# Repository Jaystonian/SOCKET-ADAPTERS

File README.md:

# SOCKET-ADAPTERS
Various adapters for ICs

23xxxAdapter: Eprom 27128/27256/27512 (28pin) to a 2332 or 2364 socket (24pin)

27xxx_to_27c080: Eprom 27c010 to 27c080 (32pin) to a 27256 or 27512 socket (28pin)

6502-65816: CPU WDC65C816 (16bit) to a 6502 (VIC-20, PET)

74LS12: Recreated the 7412 (discontinued) with a 7411 and 7406.  Use LS, HCT, AHCT or LV-A.

DIP48-XC9572XL: Xilinx CPLD to fit 48pin for C128 MMU, PLA etc.

LM323K: Triple TO-220 to fit a TO-3 (VIC-20 regulator replacement)

dipXXsoic: Fit soic-XX to dip-XX
dipXXtssop: fit tssop-XX to dip-XX
dip20soic573-373: Fit an SOIC-20 74573 to a DIP-20 74373 socket.
dip20tssop573-373: Fit a TSSOP-20 74573 to a DIP-20 74373 socket.

pi1541translator: Fit a TXS0104 4-bit level translator to a Raspberry Pi 1541 PCB as the translator unit

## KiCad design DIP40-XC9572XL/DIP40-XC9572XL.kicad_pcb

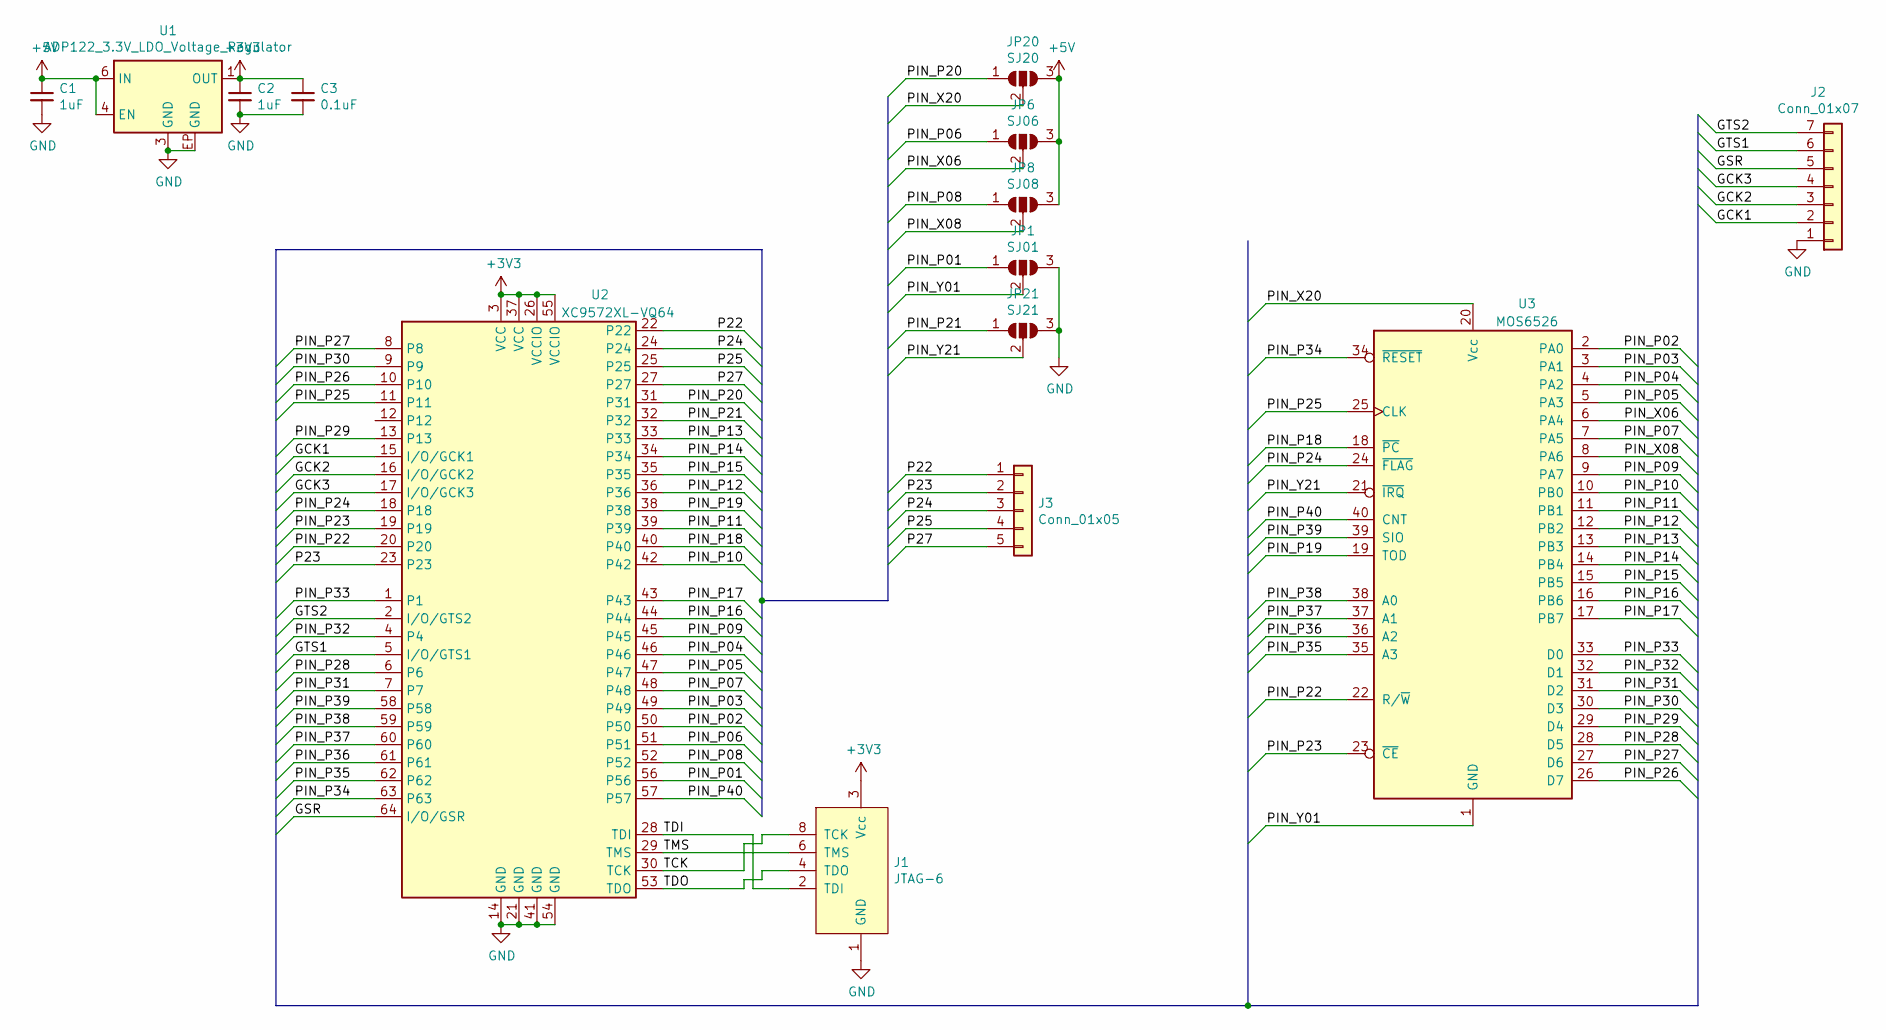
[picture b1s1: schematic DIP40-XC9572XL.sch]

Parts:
C1, C2: 1uF; C_0805_2012Metric_Pad1.15x1.40mm_HandSolder
C3: 0.1uF; C_0805_2012Metric_Pad1.15x1.40mm_HandSolder
J1: JTAG-6; PinHeader_2x04_P2.54mm_Vertical
J2: Conn_01x07; PinHeader_1x07_P2.54mm_Vertical_SMD_Pin1Right
J3: Conn_01x05; PinHeader_1x05_P1.27mm_Vertical
JP1: SJ01; SolderJumper-3_P1.3mm_Open_RoundedPad1.0x1.5mm_NumberLabels
JP6: SJ06; SolderJumper-3_P1.3mm_Open_RoundedPad1.0x1.5mm_NumberLabels
JP8: SJ08; SolderJumper-3_P1.3mm_Open_RoundedPad1.0x1.5mm_NumberLabels
JP20: SJ20; SolderJumper-3_P1.3mm_Open_RoundedPad1.0x1.5mm_NumberLabels
JP21: SJ21; SolderJumper-3_P1.3mm_Open_RoundedPad1.0x1.5mm_NumberLabels
U1: ADP122_3.3V_LDO_Voltage_Regulator; LFCSP-6
U2: XC9572XL-VQ64; TQFP-64_10x10mm_P0.5mm
U3: MOS6526; DIP-40_W15.24mm

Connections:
+3V3: C2.1, C3.1, J1.3 (Vcc), U1.1 (OUT), U2.3 (VCC), U2.26 (VCCIO), U2.37 (VCC), U2.55 (VCCIO)
+5V: C1.1, JP6.3 (B), JP8.3 (B), JP20.3 (B), U1.4 (EN), U1.6 (IN)
/GCK1: J2.2, U2.15 (I/O/GCK1)
/GCK2: J2.3, U2.16 (I/O/GCK2)
/GCK3: J2.4, U2.17 (I/O/GCK3)
/GSR: J2.5, U2.64 (I/O/GSR)
/GTS1: J2.6, U2.5 (I/O/GTS1)
/GTS2: J2.7, U2.2 (I/O/GTS2)
/P22: J3.1, U2.22
/P23: J3.2, U2.23
/P24: J3.3, U2.24
/P25: J3.4, U2.25
/P27: J3.5, U2.27
/PIN_P01: JP1.1 (A), U2.56
/PIN_P02: U2.50, U3.2 (PA0)
/PIN_P03: U2.49, U3.3 (PA1)
/PIN_P04: U2.46, U3.4 (PA2)
/PIN_P05: U2.47, U3.5 (PA3)
/PIN_P06: JP6.1 (A), U2.51
/PIN_P07: U2.48, U3.7 (PA5)
/PIN_P08: JP8.1 (A), U2.52
/PIN_P09: U2.45, U3.9 (PA7)
/PIN_P10: U2.42, U3.10 (PB0)
/PIN_P11: U2.39, U3.11 (PB1)
/PIN_P12: U2.36, U3.12 (PB2)
/PIN_P13: U2.33, U3.13 (PB3)
/PIN_P14: U2.34, U3.14 (PB4)
/PIN_P15: U2.35, U3.15 (PB5)
/PIN_P16: U2.44, U3.16 (PB6)
/PIN_P17: U2.43, U3.17 (PB7)
/PIN_P18: U2.40, U3.18 (~PC~)
/PIN_P19: U2.38, U3.19 (TOD)
/PIN_P20: JP20.1 (A), U2.31
/PIN_P21: JP21.1 (A), U2.32
/PIN_P22: U2.20, U3.22 (R/~W~)
/PIN_P23: U2.19, U3.23 (~CE~)
/PIN_P24: U2.18, U3.24 (~FLAG~)
/PIN_P25: U2.11, U3.25 (CLK)
/PIN_P26: U2.10, U3.26 (D7)
/PIN_P27: U2.8, U3.27 (D6)
/PIN_P28: U2.6, U3.28 (D5)
/PIN_P29: U2.13, U3.29 (D4)
/PIN_P30: U2.9, U3.30 (D3)
/PIN_P31: U2.7, U3.31 (D2)
/PIN_P32: U2.4, U3.32 (D1)
/PIN_P33: U2.1, U3.33 (D0)
/PIN_P34: U2.63, U3.34 (~RESET~)
/PIN_P35: U2.62, U3.35 (A3)
/PIN_P36: U2.61, U3.36 (A2)
/PIN_P37: U2.60, U3.37 (A1)
/PIN_P38: U2.59, U3.38 (A0)
/PIN_P39: U2.58, U3.39 (SIO)
/PIN_P40: U2.57, U3.40 (CNT)
/PIN_X06: JP6.2 (C), U3.6 (PA4)
/PIN_X08: JP8.2 (C), U3.8 (PA6)
/PIN_X20: JP20.2 (C), U3.20 (Vcc)
/PIN_Y01: JP1.2 (C), U3.1 (GND)
/PIN_Y21: JP21.2 (C), U3.21 (~IRQ~)
/TCK: J1.8 (TCK), U2.30 (TCK)
/TDI: J1.2 (TDI), U2.28 (TDI)
/TDO: J1.4 (TDO), U2.53 (TDO)
/TMS: J1.6 (TMS), U2.29 (TMS)
GND: C1.2, C2.2, C3.2, J1.1 (GND), J2.1, JP1.3 (B), JP21.3 (B), U1.3 (GND), U1.EP (GND), U2.14 (GND), U2.21 (GND), U2.41 (GND), U2.54 (GND)

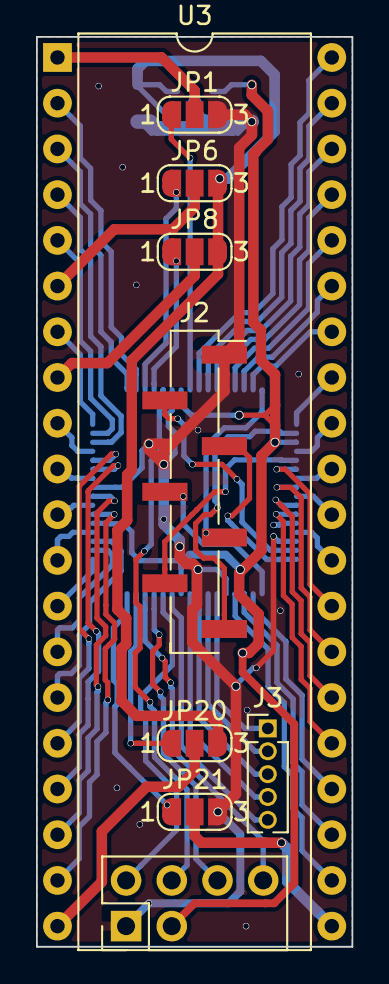
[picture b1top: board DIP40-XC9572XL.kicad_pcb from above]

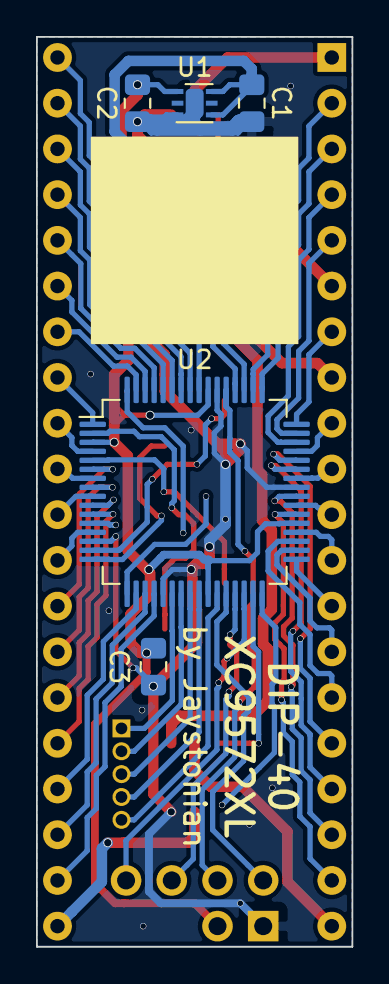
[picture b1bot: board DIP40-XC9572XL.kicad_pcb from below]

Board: 2 copper layers, 17.5 x 50.5 mm, 14 parts (5 on the bottom side), 63 nets.

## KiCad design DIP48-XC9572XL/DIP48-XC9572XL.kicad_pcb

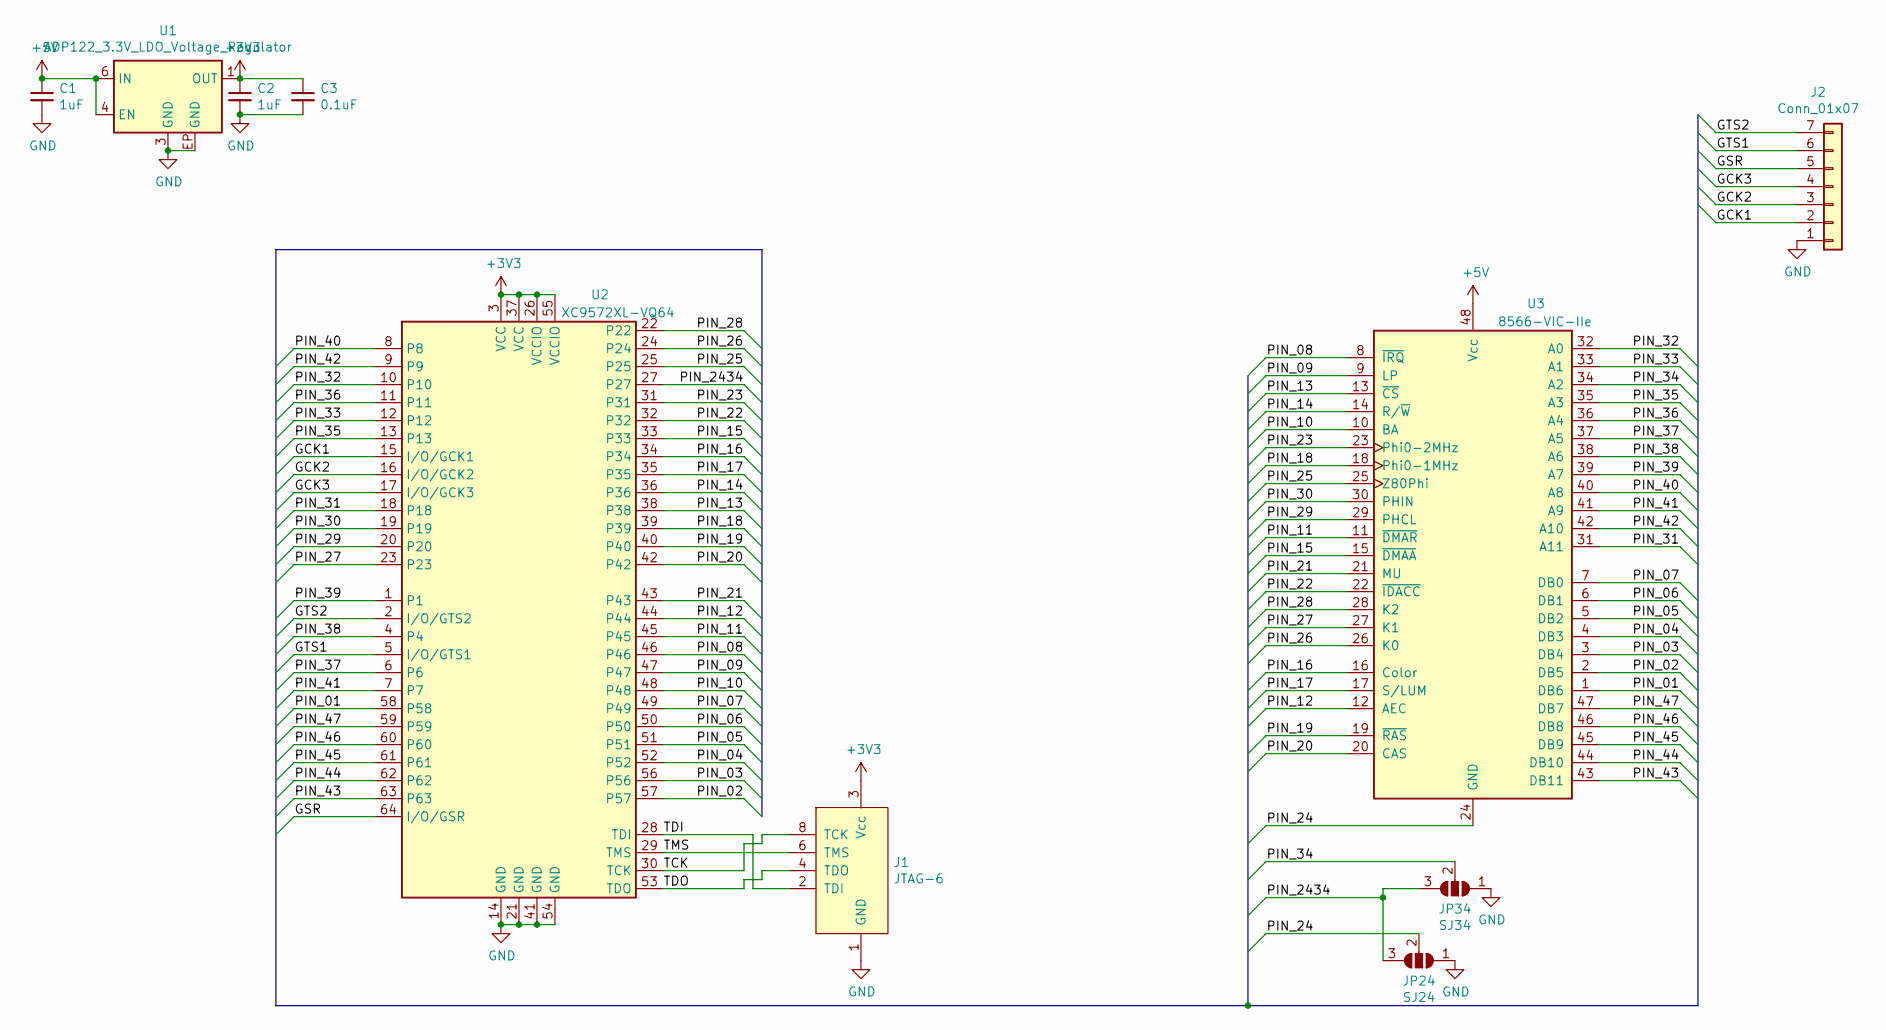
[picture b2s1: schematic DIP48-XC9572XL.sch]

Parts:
C1, C2: 1uF; C_0805_2012Metric_Pad1.15x1.40mm_HandSolder
C3: 0.1uF; C_0805_2012Metric_Pad1.15x1.40mm_HandSolder
J1: JTAG-6; PinHeader_2x04_P2.54mm_Vertical
J2: Conn_01x07; PinHeader_1x07_P2.54mm_Vertical_SMD_Pin1Right
JP24: SJ24; SolderJumper-3_P1.3mm_Open_RoundedPad1.0x1.5mm_NumberLabels
JP34: SJ34; SolderJumper-3_P1.3mm_Open_RoundedPad1.0x1.5mm_NumberLabels
U1: ADP122_3.3V_LDO_Voltage_Regulator; LFCSP-6
U2: XC9572XL-VQ64; TQFP-64_10x10mm_P0.5mm
U3: 8566-VIC-IIe; DIP-48_W15.24mm

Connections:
+3V3: C2.1, C3.1, J1.3 (Vcc), U1.1 (OUT), U2.3 (VCC), U2.26 (VCCIO), U2.37 (VCC), U2.55 (VCCIO)
+5V: C1.1, U1.4 (EN), U1.6 (IN), U3.48 (Vcc)
/GCK1: J2.2, U2.15 (I/O/GCK1)
/GCK2: J2.3, U2.16 (I/O/GCK2)
/GCK3: J2.4, U2.17 (I/O/GCK3)
/GSR: J2.5, U2.64 (I/O/GSR)
/GTS1: J2.6, U2.5 (I/O/GTS1)
/GTS2: J2.7, U2.2 (I/O/GTS2)
/PIN_01: U2.58, U3.1 (DB6)
/PIN_02: U2.57, U3.2 (DB5)
/PIN_03: U2.56, U3.3 (DB4)
/PIN_04: U2.52, U3.4 (DB3)
/PIN_05: U2.51, U3.5 (DB2)
/PIN_06: U2.50, U3.6 (DB1)
/PIN_07: U2.49, U3.7 (DB0)
/PIN_08: U2.46, U3.8 (~IRQ~)
/PIN_09: U2.47, U3.9 (LP)
/PIN_10: U2.48, U3.10 (BA)
/PIN_11: U2.45, U3.11 (~DMAR)
/PIN_12: U2.44, U3.12 (AEC)
/PIN_13: U2.38, U3.13 (~CS~)
/PIN_14: U2.36, U3.14 (R/~W~)
/PIN_15: U2.33, U3.15 (~DMAA)
/PIN_16: U2.34, U3.16 (Color)
/PIN_17: U2.35, U3.17 (S/LUM)
/PIN_18: U2.39, U3.18 (Phi0-1MHz)
/PIN_19: U2.40, U3.19 (~RAS~)
/PIN_20: U2.42, U3.20 (CAS)
/PIN_21: U2.43, U3.21 (MU)
/PIN_22: U2.32, U3.22 (~IDACC)
/PIN_23: U2.31, U3.23 (Phi0-2MHz)
/PIN_24: JP24.2 (C), U3.24 (GND)
/PIN_25: U2.25, U3.25 (Z80Phi)
/PIN_26: U2.24, U3.26 (K0)
/PIN_27: U2.23, U3.27 (K1)
/PIN_28: U2.22, U3.28 (K2)
/PIN_29: U2.20, U3.29 (PHCL)
/PIN_30: U2.19, U3.30 (PHIN)
/PIN_31: U2.18, U3.31 (A11)
/PIN_32: U2.10, U3.32 (A0)
/PIN_33: U2.12, U3.33 (A1)
/PIN_34: JP34.2 (C), U3.34 (A2)
/PIN_35: U2.13, U3.35 (A3)
/PIN_36: U2.11, U3.36 (A4)
/PIN_37: U2.6, U3.37 (A5)
/PIN_38: U2.4, U3.38 (A6)
/PIN_39: U2.1, U3.39 (A7)
/PIN_40: U2.8, U3.40 (A8)
/PIN_41: U2.7, U3.41 (A9)
/PIN_42: U2.9, U3.42 (A10)
/PIN_43: U2.63, U3.43 (DB11)
/PIN_44: U2.62, U3.44 (DB10)
/PIN_45: U2.61, U3.45 (DB9)
/PIN_46: U2.60, U3.46 (DB8)
/PIN_47: U2.59, U3.47 (DB7)
/PIN_2434: JP24.3 (B), JP34.3 (B), U2.27
/TCK: J1.8 (TCK), U2.30 (TCK)
/TDI: J1.2 (TDI), U2.28 (TDI)
/TDO: J1.4 (TDO), U2.53 (TDO)
/TMS: J1.6 (TMS), U2.29 (TMS)
GND: C1.2, C2.2, C3.2, J1.1 (GND), J2.1, JP24.1 (A), JP34.1 (A), U1.3 (GND), U1.EP (GND), U2.14 (GND), U2.21 (GND), U2.41 (GND), U2.54 (GND)

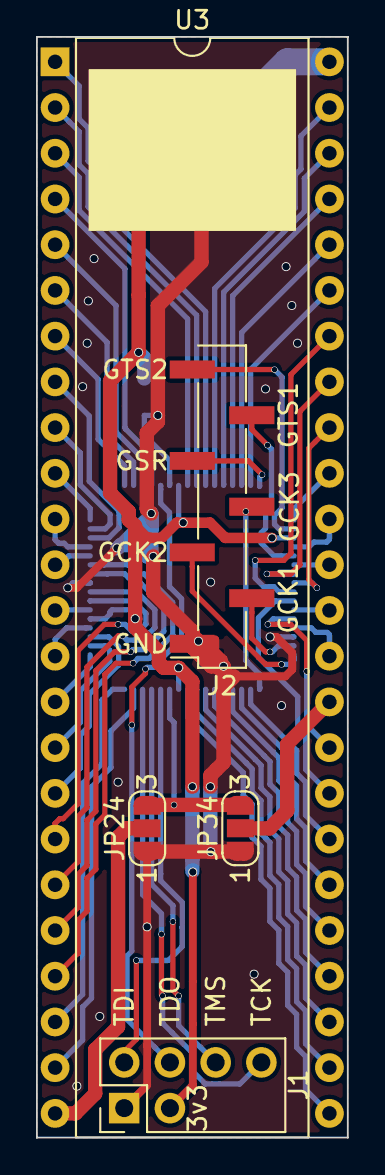
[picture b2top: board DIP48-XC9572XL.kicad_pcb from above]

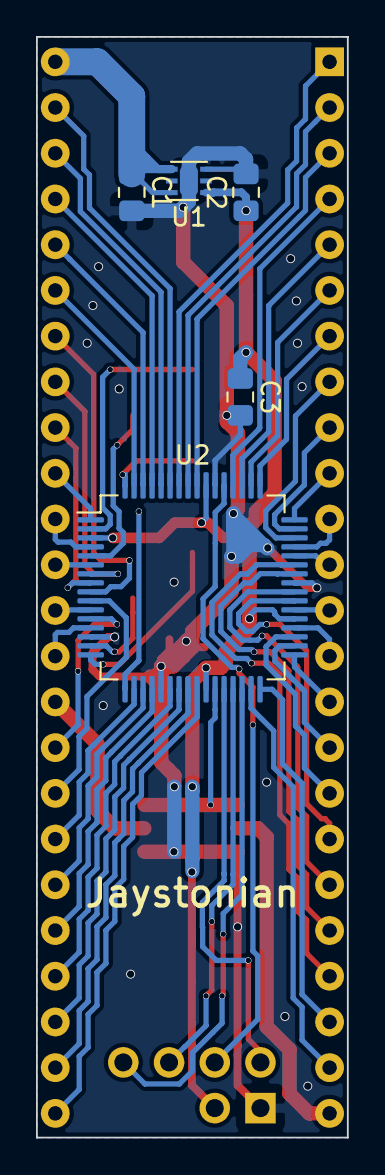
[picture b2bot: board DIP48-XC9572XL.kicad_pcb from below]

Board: 2 copper layers, 17.3 x 61.2 mm, 10 parts (5 on the bottom side), 61 nets.

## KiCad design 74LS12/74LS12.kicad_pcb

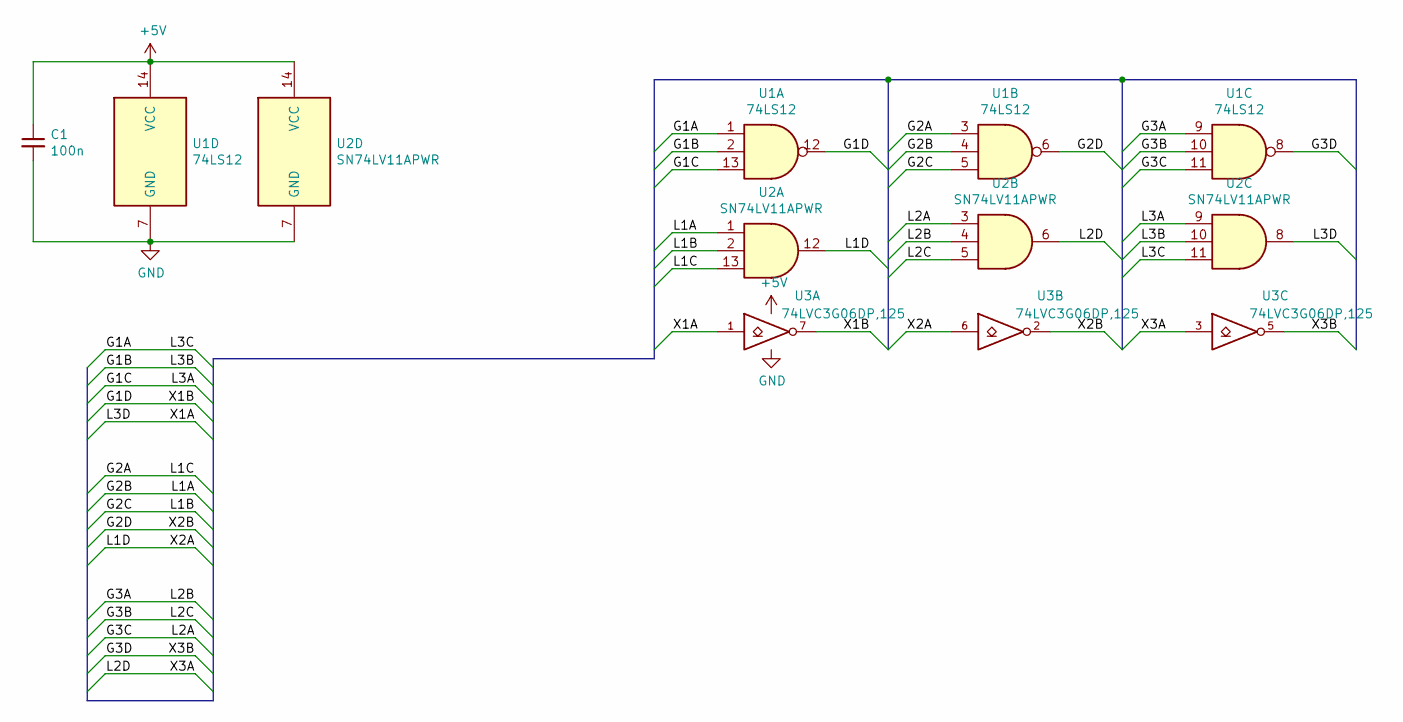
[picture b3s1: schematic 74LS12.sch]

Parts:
C1: 100n; C_0805_2012Metric_Pad1.15x1.40mm_HandSolder
U1: 74LS12; DIP-14_W7.62mm
U2: SN74LV11APWR; TSSOP-14_4.4x5mm_P0.65mm
U3: 74LVC3G06DP,125; TSSOP-8_3x3mm_P0.65mm

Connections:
+5V: C1.1, U1.14 (VCC), U2.14 (VCC), U3.8 (VCC)
/G1A: U1.1, U2.11
/G1B: U1.2, U2.10
/G1C: U1.13, U2.9
/G1D: U1.12, U3.7
/G2A: U1.3, U2.13
/G2B: U1.4, U2.1
/G2C: U1.5, U2.2
/G2D: U1.6, U3.2
/G3A: U1.9, U2.4
/G3B: U1.10, U2.5
/G3C: U1.11, U2.3
/G3D: U1.8, U3.5
/L1D: U2.12, U3.6
/L2D: U2.6, U3.3
/L3D: U2.8, U3.1
GND: C1.2, U1.7 (GND), U2.7 (GND), U3.4 (GND)

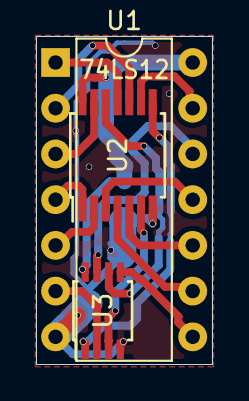
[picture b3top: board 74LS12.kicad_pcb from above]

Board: 2 copper layers, 9.8 x 18.2 mm, 4 parts (1 on the bottom side), 17 nets.

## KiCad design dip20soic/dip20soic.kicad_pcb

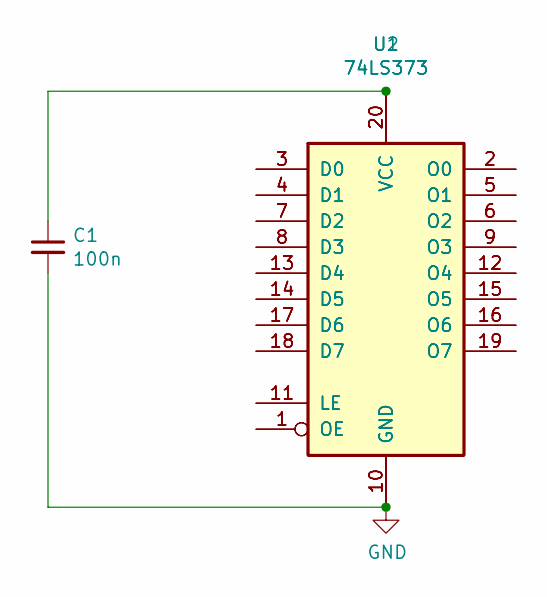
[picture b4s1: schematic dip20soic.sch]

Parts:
C1: 100n; C_0805_2012Metric_Pad1.15x1.40mm_HandSolder
U1: 74LS373; DIP-20_W7.62mm
U2: 74LS373; SOIC-20W_7.5x12.8mm_P1.27mm

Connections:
GND: C1.2, U1.10 (GND), U2.10 (GND)
unnamed: C1.1, U1.20 (VCC), U2.20 (VCC)
unnamed: U1.1 (OE), U2.1 (OE)
unnamed: U1.2 (O0), U2.2 (O0)
unnamed: U1.3 (D0), U2.3 (D0)
unnamed: U1.4 (D1), U2.4 (D1)
unnamed: U1.5 (O1), U2.5 (O1)
unnamed: U1.6 (O2), U2.6 (O2)
unnamed: U1.7 (D2), U2.7 (D2)
unnamed: U1.8 (D3), U2.8 (D3)
unnamed: U1.9 (O3), U2.9 (O3)
unnamed: U1.11 (LE), U2.11 (LE)
unnamed: U1.12 (O4), U2.12 (O4)
unnamed: U1.13 (D4), U2.13 (D4)
unnamed: U1.14 (D5), U2.14 (D5)
unnamed: U1.15 (O5), U2.15 (O5)
unnamed: U1.16 (O6), U2.16 (O6)
unnamed: U1.17 (D6), U2.17 (D6)
unnamed: U1.18 (D7), U2.18 (D7)
unnamed: U1.19 (O7), U2.19 (O7)

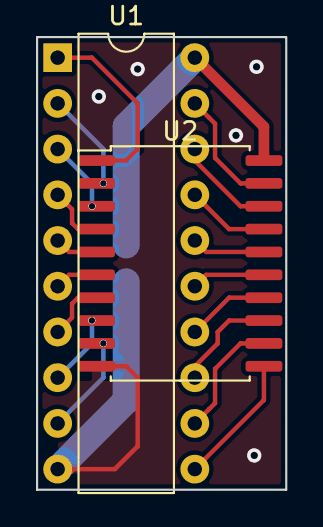
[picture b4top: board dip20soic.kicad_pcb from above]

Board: 2 copper layers, 13.8 x 25.1 mm, 3 parts (1 on the bottom side), 20 nets.

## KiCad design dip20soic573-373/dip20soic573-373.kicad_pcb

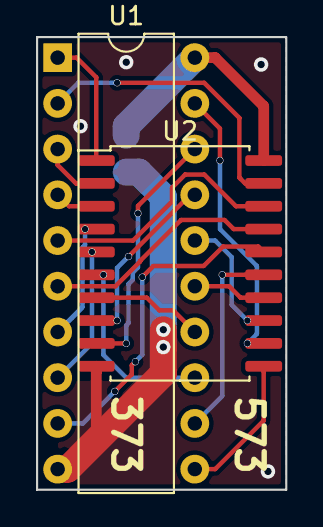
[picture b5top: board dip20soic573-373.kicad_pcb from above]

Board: 2 copper layers, 13.8 x 25.1 mm, 3 parts (1 on the bottom side), 20 nets.

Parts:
C1: 100n; C_0805_2012Metric_Pad1.15x1.40mm_HandSolder
U1: 74LS373; DIP-20_W7.62mm
U2: 74LS573; SOIC-20W_7.5x12.8mm_P1.27mm

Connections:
GND: C1.2, U1.10, U2.10
unnamed: C1.1, U1.20, U2.20
unnamed: U1.1, U2.1
unnamed: U1.2, U2.19
unnamed: U1.3, U2.2
unnamed: U1.4, U2.3
unnamed: U1.5, U2.18
unnamed: U1.6, U2.17
unnamed: U1.7, U2.4
unnamed: U1.8, U2.5
unnamed: U1.9, U2.16
unnamed: U1.11, U2.11
unnamed: U1.12, U2.15
unnamed: U1.13, U2.6
unnamed: U1.14, U2.7
unnamed: U1.15, U2.14
unnamed: U1.16, U2.13
unnamed: U1.17, U2.8
unnamed: U1.18, U2.9
unnamed: U1.19, U2.12
